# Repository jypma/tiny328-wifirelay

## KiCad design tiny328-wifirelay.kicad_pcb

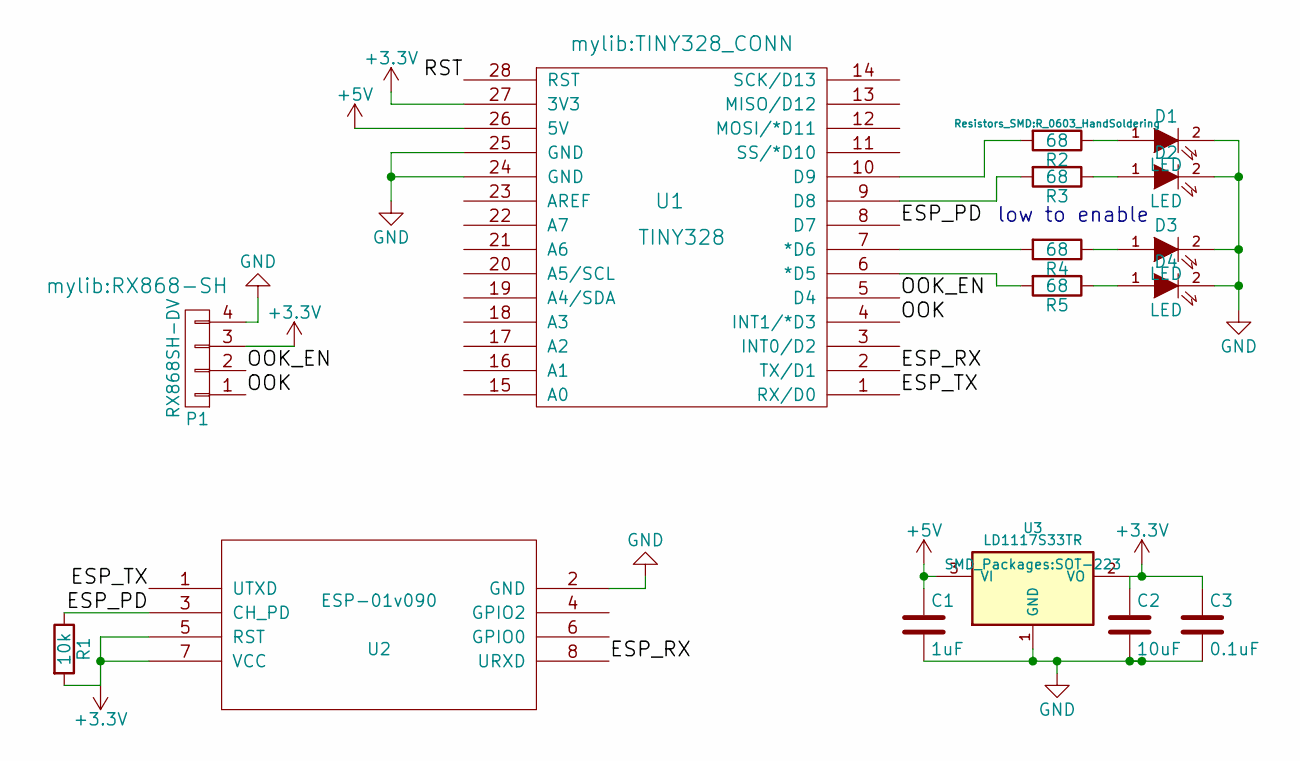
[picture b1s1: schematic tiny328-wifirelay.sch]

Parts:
C1: 1uF; C_0603_HandSoldering
C2: 10uF; C_0603_HandSoldering
C3: 0.1uF; C_0603_HandSoldering
D1, D2, D3, D4: LED; LED-0805
P1: RX868SH-DV; RX868-SH
R1: 10k; R_0603_HandSoldering
R2, R3, R4, R5: 68; R_0603_HandSoldering
U1: TINY328; TINY328_CONN
U2: ESP-01v090; ESP-01
U3: LD1117S33TR; SOT-223

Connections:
+3V3: C2.1, C3.1, P1.3, R1.2, U1.27 (3V3), U2.5 (RST), U2.7 (VCC), U3.2 (VO)
+5V: C1.1, U1.26 (5V), U3.3 (VI)
/ESP_PD: R1.1, U1.8 (D7), U2.3 (CH_PD)
/ESP_RX: U1.2 (TX/D1), U2.8 (URXD)
/ESP_TX: U1.1 (RX/D0), U2.1 (UTXD)
/OOK: P1.1, U1.4 (INT1/*D3)
/OOK_EN: P1.2, U1.5 (D4)
/RST: U1.28 (RST)
GND: C1.2, C2.2, C3.2, D1.2 (K), D2.2 (K), D3.2 (K), D4.2 (K), P1.4, U1.24 (GND), U1.25 (GND), U2.2 (GND), U3.1 (GND)
unnamed: D1.1 (A), R2.1
unnamed: D2.1 (A), R3.1
unnamed: D3.1 (A), R4.1
unnamed: D4.1 (A), R5.1
unnamed: R2.2, U1.10 (D9)
unnamed: R3.2, U1.9 (D8)
unnamed: R4.2, U1.7 (*D6)
unnamed: R5.2, U1.6 (*D5)

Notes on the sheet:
low to enable

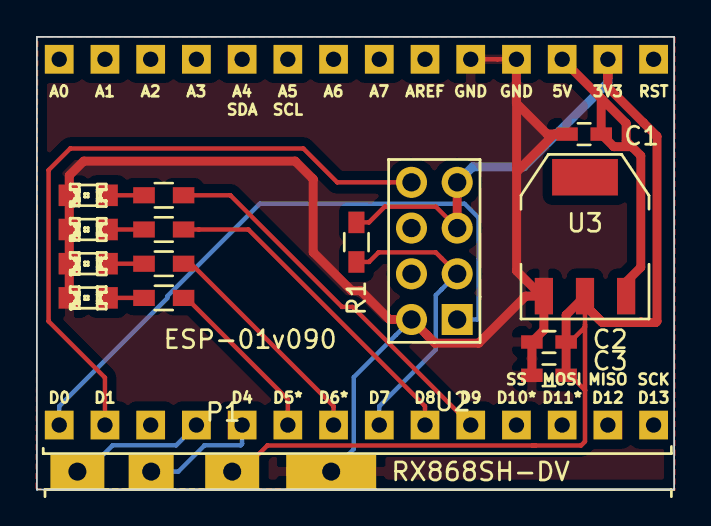
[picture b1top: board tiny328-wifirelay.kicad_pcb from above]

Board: 2 copper layers, 35.4 x 25.2 mm, 16 parts (0 on the bottom side), 16 nets.

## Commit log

2015-09-03 initial commit for Wifi RFM12 / OOK relay
2015-10-28 updated for PCB run #1
2015-12-30 Add firmware based on AvrLib
2015-12-30 Fix ESP initialization
    We do this by pulling down CH_PD, such that the ESP doesn't start booting
    until the AtMega tells it to.
